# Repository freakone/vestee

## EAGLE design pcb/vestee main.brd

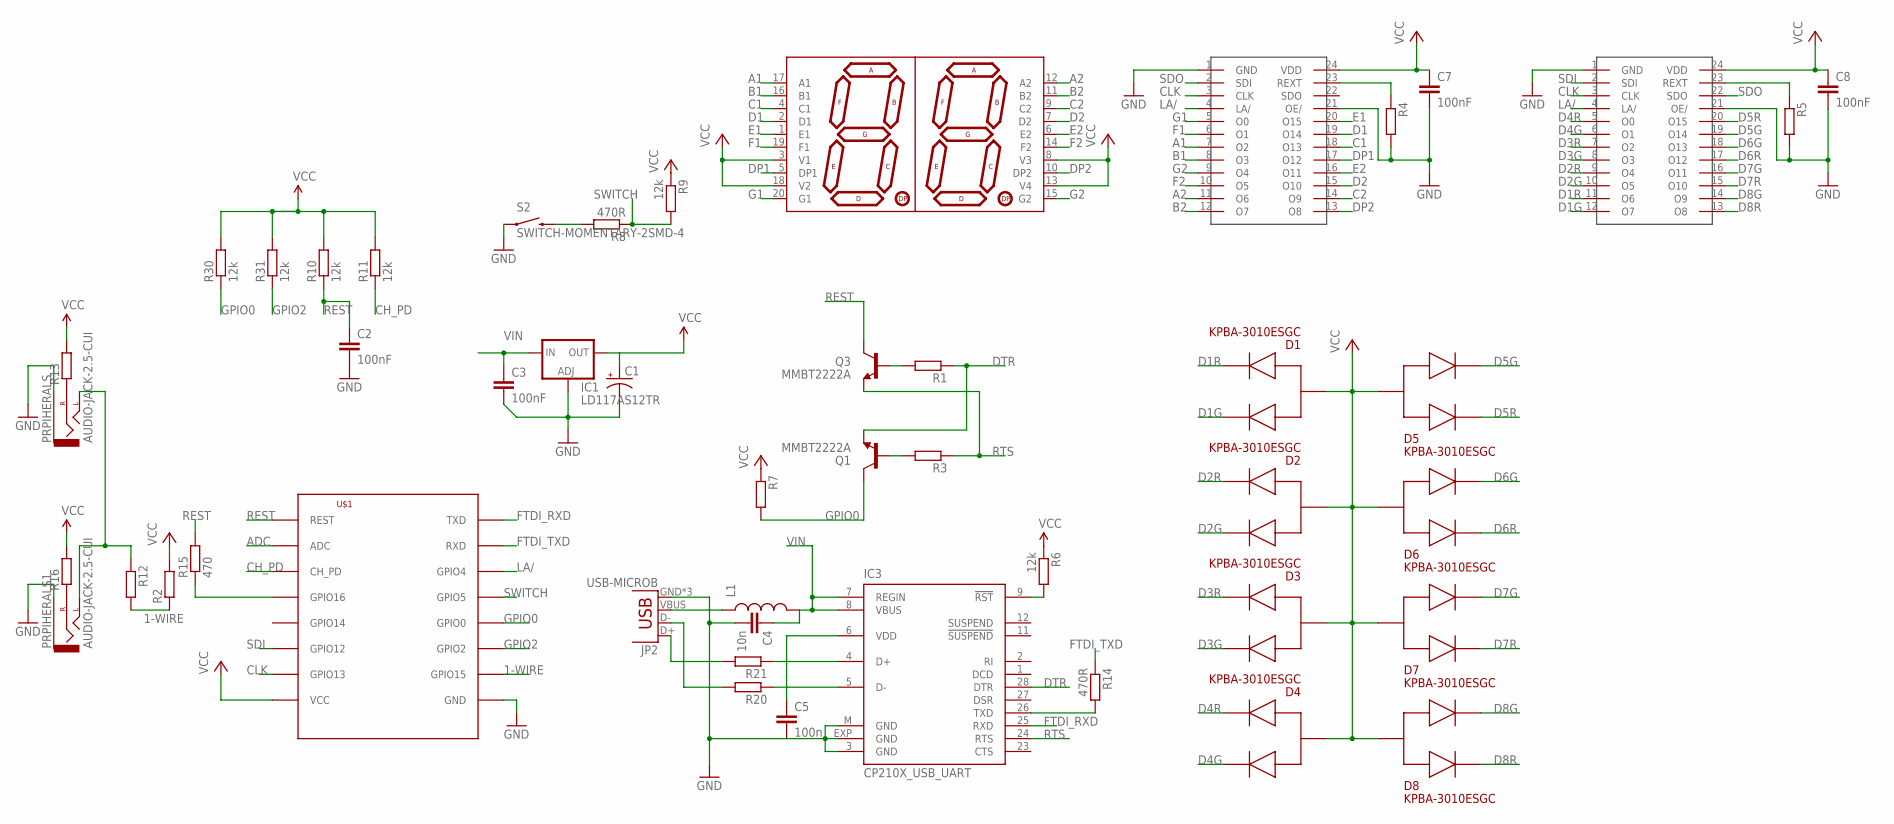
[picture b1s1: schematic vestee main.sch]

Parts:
C1: CAP_POL3528; EIA3528
C2, C3, C7, C8: 100nF; C0603
C4: 10n; C0603
C5: 100n; C0603
D1, D2, D3, D4, D5, D6, D7, D8: KPBA-3010ESGC; APA3010SF4C
IC1: LD117AS12TR; SOT223
IC3: CP210X_USB_UART; MLP28
JP2: USB-MICROB
L1: INDUCTOR1210; 1210
PRPIHERALS, PRPIHERALS1: AUDIO-JACK-2.5-CUI; STEREOJACK2.5_SMD_CUI
Q1, Q3: MMBT2222A; SOT23-3
R1, R2, R3, R4, R5, R7, R12, R20, R21: R-EU_R0603; R0603
R6, R9, R10, R11, R30, R31: 12k; R0603
R8, R14: 470R; R0603
R13, R16: R-EU_M1206; M1206
R15: 470; R0603
S2: SWITCH-MOMENTARY-2SMD-4; TACTILE_SWITCH_TALL
U$1: ESP8266-07; ESP-07
U$2: KCDA02-103
U$3, U$4: SCT2024CSSG; SSOP24

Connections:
1-WIRE: R2.1, R12.2, U$1.GPIO15
A1: U$2.17 (A1), U$3.7 (O2)
A2: U$2.12 (A2), U$3.11 (O6)
ADC: U$1.ADC
B1: U$2.16 (B1), U$3.8 (O3)
B2: U$2.11 (B2), U$3.12 (O7)
C1: U$2.4 (C1), U$3.18 (O13)
C2: U$2.9 (C2), U$3.14 (O9)
CH_PD: R11.1, U$1.CH_PD
CLK: U$1.GPIO13, U$3.3 (CLK), U$4.3 (CLK)
D1: U$2.2 (D1), U$3.19 (O14)
D1G: D1.3, U$4.12 (O7)
D1R: D1.2, U$4.11 (O6)
D2: U$2.7 (D2), U$3.15 (O10)
D2G: D2.3, U$4.10 (O5)
D2R: D2.2, U$4.9 (O4)
D3G: D3.3, U$4.8 (O3)
D3R: D3.2, U$4.7 (O2)
D4G: D4.3, U$4.6 (O1)
D4R: D4.2, U$4.5 (O0)
D5G: D5.3, U$4.19 (O14)
D5R: D5.2, U$4.20 (O15)
D6G: D6.3, U$4.18 (O13)
D6R: D6.2, U$4.17 (O12)
D7G: D7.3, U$4.16 (O11)
D7R: D7.2, U$4.15 (O10)
D8G: D8.3, U$4.14 (O9)
D8R: D8.2, U$4.13 (O8)
DP1: U$2.5 (DP1), U$3.17 (O12)
DP2: U$2.10 (DP2), U$3.13 (O8)
DTR: IC3.28 (DTR), Q1.2 (E), R1.1
E1: U$2.1 (E1), U$3.20 (O15)
E2: U$2.6 (E2), U$3.16 (O11)
F1: U$2.19 (F1), U$3.6 (O1)
F2: U$2.14 (F2), U$3.10 (O5)
FTDI_RXD: IC3.25 (RXD), U$1.TXD
FTDI_TXD: R14.1, U$1.RXD
G1: U$2.20 (G1), U$3.5 (O0)
G2: U$2.15 (G2), U$3.9 (O4)
GND: C1.C (-), C2.2, C3.2, C4.2, C5.2, C7.2, C8.2, IC1.1 (ADJ), IC3.3 (GND), IC3.EXP (GND), IC3.M (GND), JP2.GND, JP2.MT1 (GND), JP2.MT2 (GND), PRPIHERALS.1 (SLEEVE), PRPIHERALS1.1 (SLEEVE), R4.2, R5.2, S2.A2 (1), U$1.GND, U$3.1 (GND), U$3.21 (OE/), U$4.1 (GND), U$4.21 (OE/)
GPIO0: Q1.3 (C), R7.2, R30.1, U$1.GPIO0
GPIO2: R31.1, U$1.GPIO2
GPIO16: R15.1, U$1.GPIO16
JACK: PRPIHERALS.3 (LEFT), PRPIHERALS1.3 (LEFT), R12.1
LA/: U$1.GPIO4, U$3.4 (LA/), U$4.4 (LA/)
unnamed: R4.1, U$3.23 (REXT)
unnamed: JP2.D+, R21.2
unnamed: JP2.D-, R20.2
unnamed: R5.1, U$4.23 (REXT)
unnamed: Q3.1 (B), R1.2
unnamed: PRPIHERALS.2 (RIGHT), R13.1
unnamed: JP2.VBUS, L1.1
unnamed: PRPIHERALS1.2 (RIGHT), R16.1
unnamed: C5.1, IC3.6 (VDD)
unnamed: IC3.9 (!RST), R6.2
unnamed: Q1.1 (B), R3.2
unnamed: R8.2, S2.B2 (2)
unnamed: IC3.4 (D+), R21.1
unnamed: IC3.5 (D-), R20.1
REST: C2.1, Q3.3 (C), R10.1, R15.2, U$1.REST
RTS: IC3.24 (RTS), Q3.2 (E), R3.1
SDI: U$1.GPIO12, U$4.2 (SDI)
SDO: U$3.2 (SDI), U$4.22 (SDO)
SWITCH: R8.1, R9.2, U$1.GPIO5
TXD: IC3.26 (TXD), R14.2
VCC: C1.A (+), C7.1, C8.1, D1.COM, D2.COM, D3.COM, D4.COM, D5.COM, D6.COM, D7.COM, D8.COM, IC1.4 (OUT), R2.2, R6.1, R7.1, R9.1, R10.2, R11.2, R13.2, R16.2, R30.2, R31.2, U$1.VCC, U$2.3 (V1), U$2.8 (V3), U$2.13 (V4), U$2.18 (V2), U$3.24 (VDD), U$4.24 (VDD)
VIN: C3.1, C4.1, IC1.3 (IN), IC3.7 (REGIN), IC3.8 (VBUS), L1.2

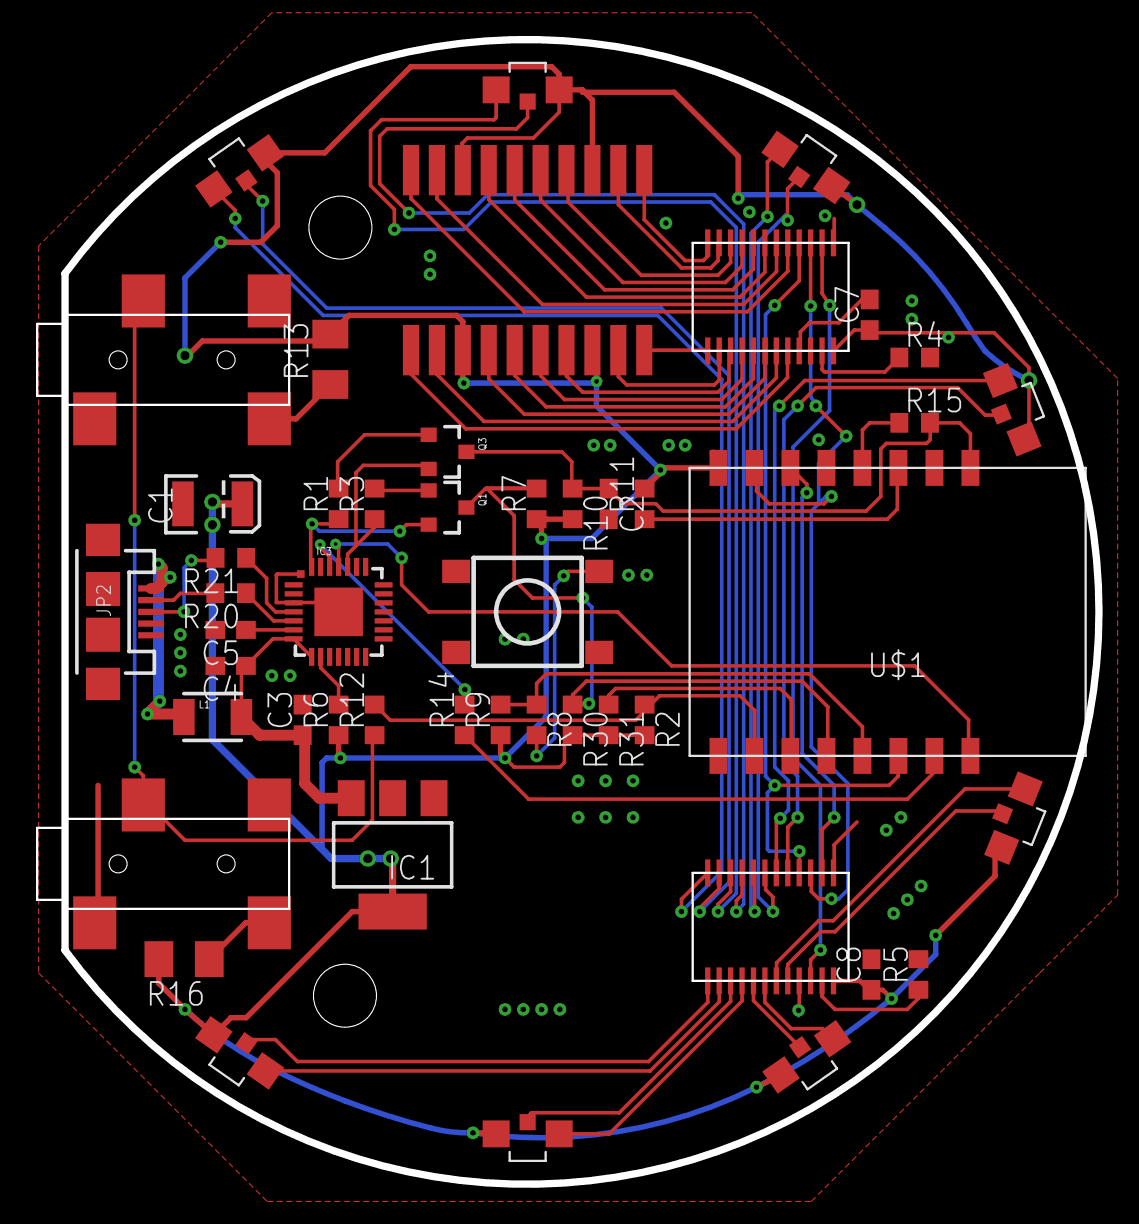
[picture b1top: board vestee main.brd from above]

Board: 2 copper layers, 58.9 x 63.6 mm, 48 parts (0 on the bottom side), 66 nets.

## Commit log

2015-11-16 prototype board
2016-01-10 Fixed discovered issues, removed DC jack, added jack for 1-Wire, minor improvements
2016-01-10 Fixed silkscreen
2016-01-10 fixed text under logo
2016-01-11 Added new LED to GPIO12, screw holes, bottom layer fixes
2016-01-11 Moved button to the center
2016-01-12 Add VCC pads, move silk
2016-02-13 Version 2, all issues fixed
2016-02-23 meteor start app
2016-02-23 adding api keys
2016-02-24 device names + only self visible
2016-02-24 charts subsite
2016-02-24 highcharts example, measurements schema
2016-02-25 api for adding measurements
2016-02-26 schema naming correction, measurements splitted
2016-02-26 working charts
2016-02-26 charts labels on x-axis, width adaptation
2016-02-26 charts styling
2016-02-26 change chart type to stockchart
2016-02-26 stockchart width fix
2016-02-26 rollback to classic charts
2016-02-26 stock chart working
2016-02-26 data filler
2016-02-27 charts width responsivity
2016-02-27 charts per device display fix
2016-02-28 mobbile view tunning, form validation fix
2016-02-28 css file for mobile view
2016-02-28 esp code begin
2016-02-29 MQTT server at webservice
2016-02-29 mqtt test python script
2016-03-02 mqtt data filler
2016-03-02 report temperature every minute
2016-03-03 data fetching fx, timezone offset fix, favicon change, repo cleaning'
2016-03-03 esp fw missing function
2016-03-16 sample limit, last temperature above chart, chart mod
2016-07-11 pcb rev3
2016-07-12 Added current setting resistors for LED drivers
2016-07-12 Added logo
2016-08-13 Added Foam Sil Screen Art
2016-08-13 Silk improvements
2016-08-13 Fied tStop to bStop
2016-08-14 Rerouted bottom traces to be covered by soldermask
2016-08-24 Fix latch drivers connections, add polyfuses to jacks
2016-08-24 PCB conversion
2016-08-24 Layout adjusted to schematic bug fixes
2016-08-24 Fixes
2016-08-31 Add gerber files for pcb

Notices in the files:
parts and their libraries:
SparkFun-Connectors: Licensing: Creative Commons ShareAlike 4.0 International - https://creativecommons.org/licenses/by-sa/4.0
